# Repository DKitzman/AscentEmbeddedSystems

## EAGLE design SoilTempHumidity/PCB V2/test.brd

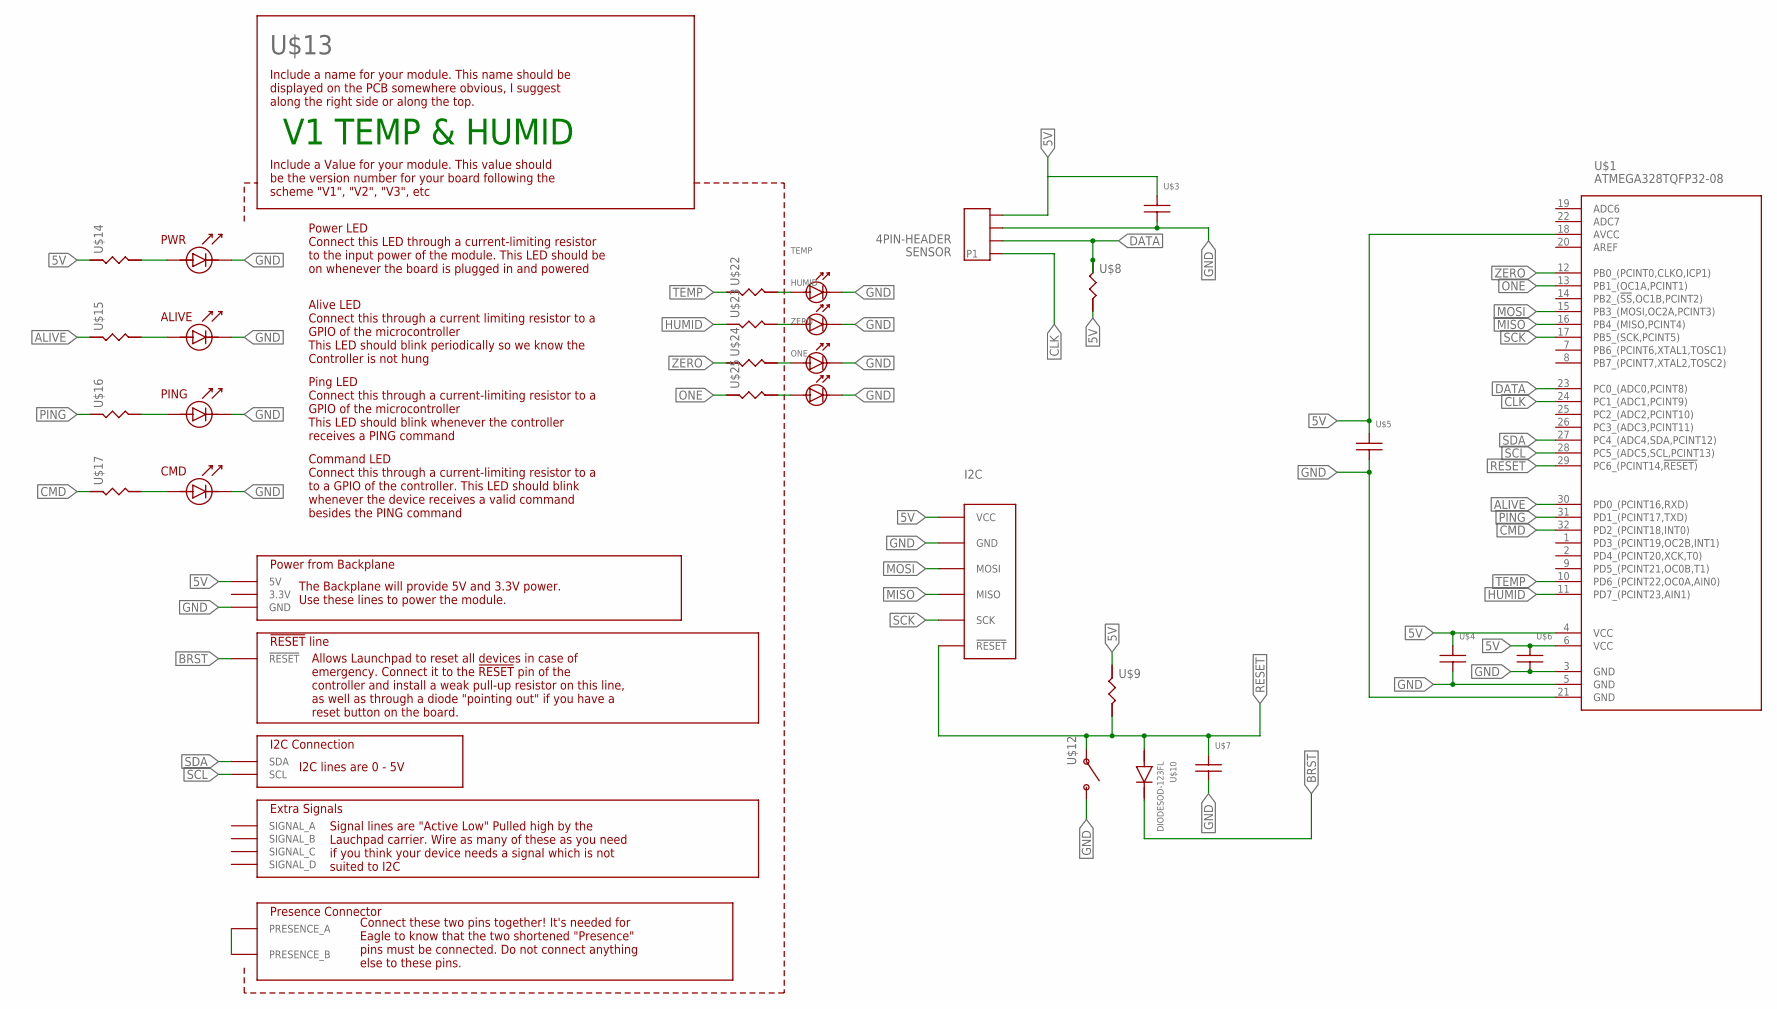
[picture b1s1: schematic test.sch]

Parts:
HUMID: LED; 0805_LED
I2C: ISP_PROGRAMMING_HEADER; 6PINHEADER_CORRECT
ONE: LED; 0805_LED
SENSOR: 4PIN-HEADER; 4HEADER_10MIL
TEMP: LED; 0805_LED
U$1: ATMEGA328TQFP32-08; TQFP32-08
U$3, U$4, U$5, U$6, U$7: CAPACITOR-UNPOLARIZED0805; 0805_STACKPOLERESISTOR
U$8, U$9, U$14, U$15, U$16, U$17, U$22, U$23, U$24, U$25: RESISTOR; 0805_STACKPOLERESISTOR
U$10: DIODESOD-123FL; SOD-123FL
U$12: PUSHBUTTONSMD; PUSHBUTTON_SMD
U$13: EMBEDDED_SUBSYSTEM_V2SMALL; SUBSYSTEM2016_V2-SMALL
ZERO: LED; 0805_LED

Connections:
5V: I2C.2 (VCC), SENSOR.P$4, U$1.4 (VCC), U$1.6 (VCC), U$1.18 (AVCC), U$3.P$1, U$4.P$1, U$5.P$1, U$6.P$1, U$8.P$2, U$9.P$1, U$13.B2 (5V), U$13.B3 (5V), U$14.P$1
ALIVE: U$1.30 (PD0_(PCINT16,RXD)), U$15.P$1
BRST: U$10.CATHODE, U$13.B5 (!RESET), U$13.B6 (!RESET)
CLK: SENSOR.P$1 (P1), U$1.24 (PC1_(ADC1,PCINT9))
CMD: U$1.32 (PD2_(PCINT18,INT0)), U$17.P$1
DATA: SENSOR.P$2, U$1.23 (PC0_(ADC0,PCINT8)), U$8.P$1
GND: HUMID.CATHODE, I2C.6 (GND), ONE.CATHODE, SENSOR.P$3, TEMP.CATHODE, U$1.3 (GND), U$1.5 (GND), U$1.21 (GND), U$3.P$2, U$4.P$2, U$5.P$2, U$6.P$2, U$7.P$2, U$12.3, U$13.A7 (GND), U$13.A8 (GND), U$13.A9 (GND), U$13.A10 (GND), U$13.ALIVELED_CATHODE, U$13.CMDLED_CATHODE, U$13.PINGLED_CATHODE, U$13.PWRLED_CATHODE, ZERO.CATHODE
HUMID: U$1.11 (PD7_(PCINT23,AIN1)), U$23.P$1
MISO: I2C.1 (MISO), U$1.16 (PB4_(MISO,PCINT4))
MOSI: I2C.4 (MOSI), U$1.15 (PB3_(MOSI,OC2A,PCINT3))
unnamed: U$13.A2 (PRESENCE_A), U$13.B17 (PRESENCE_B)
unnamed: U$13.PWRLED_ANODE, U$14.P$2
unnamed: U$13.ALIVELED_ANODE, U$15.P$2
unnamed: U$13.PINGLED_ANODE, U$16.P$2
unnamed: U$13.CMDLED_ANODE, U$17.P$2
unnamed: TEMP.ANODE, U$22.P$2
unnamed: HUMID.ANODE, U$23.P$2
unnamed: U$24.P$2, ZERO.ANODE
unnamed: ONE.ANODE, U$25.P$2
ONE: U$1.13 (PB1_(OC1A,PCINT1)), U$25.P$1
PING: U$1.31 (PD1_(PCINT17,TXD)), U$16.P$1
RESET: I2C.5 (!RESET), U$1.29 (PC6_(PCINT14,!RESET)), U$7.P$1, U$9.P$2, U$10.ANODE, U$12.1
SCK: I2C.3 (SCK), U$1.17 (PB5_(SCK,PCINT5))
SCL: U$1.28 (PC5_(ADC5,SCL,PCINT13)), U$13.B9 (SCL), U$13.B10 (SCL)
SDA: U$1.27 (PC4_(ADC4,SDA,PCINT12)), U$13.B7 (SDA), U$13.B8 (SDA)
TEMP: U$1.10 (PD6_(PCINT22,OC0A,AIN0)), U$22.P$1
ZERO: U$1.12 (PB0_(PCINT0,CLKO,ICP1)), U$24.P$1

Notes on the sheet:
V1 TEMP & HUMID

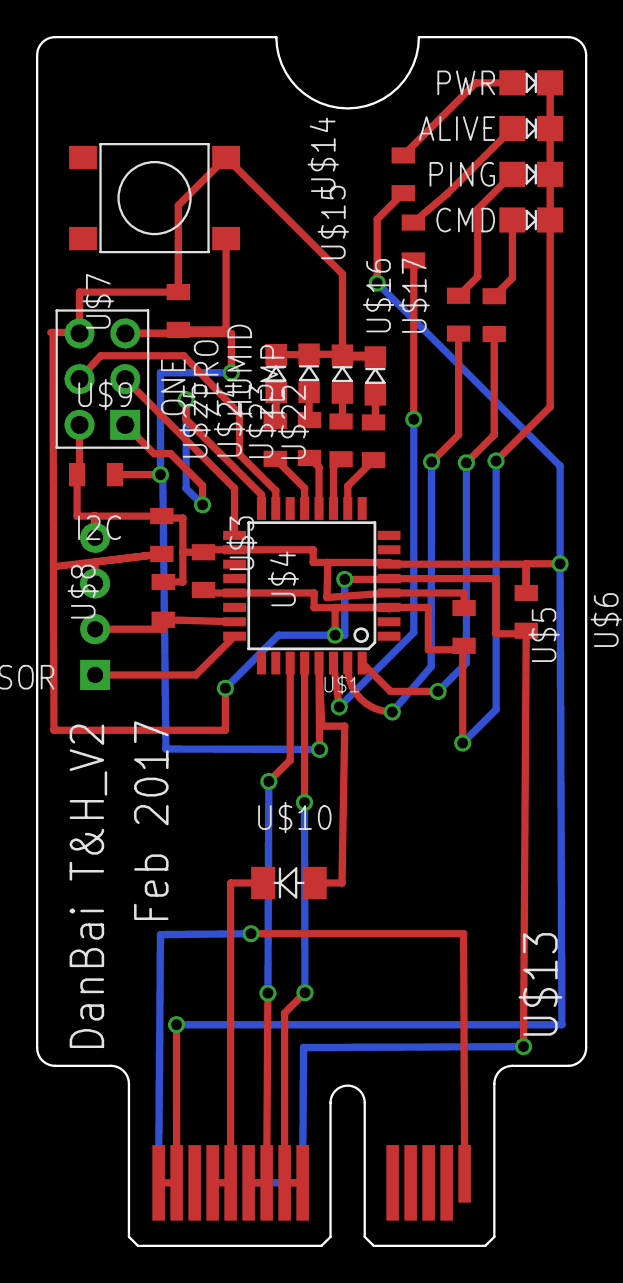
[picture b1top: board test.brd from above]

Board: 2 copper layers, 30.5 x 67.2 mm, 25 parts (0 on the bottom side), 27 nets.

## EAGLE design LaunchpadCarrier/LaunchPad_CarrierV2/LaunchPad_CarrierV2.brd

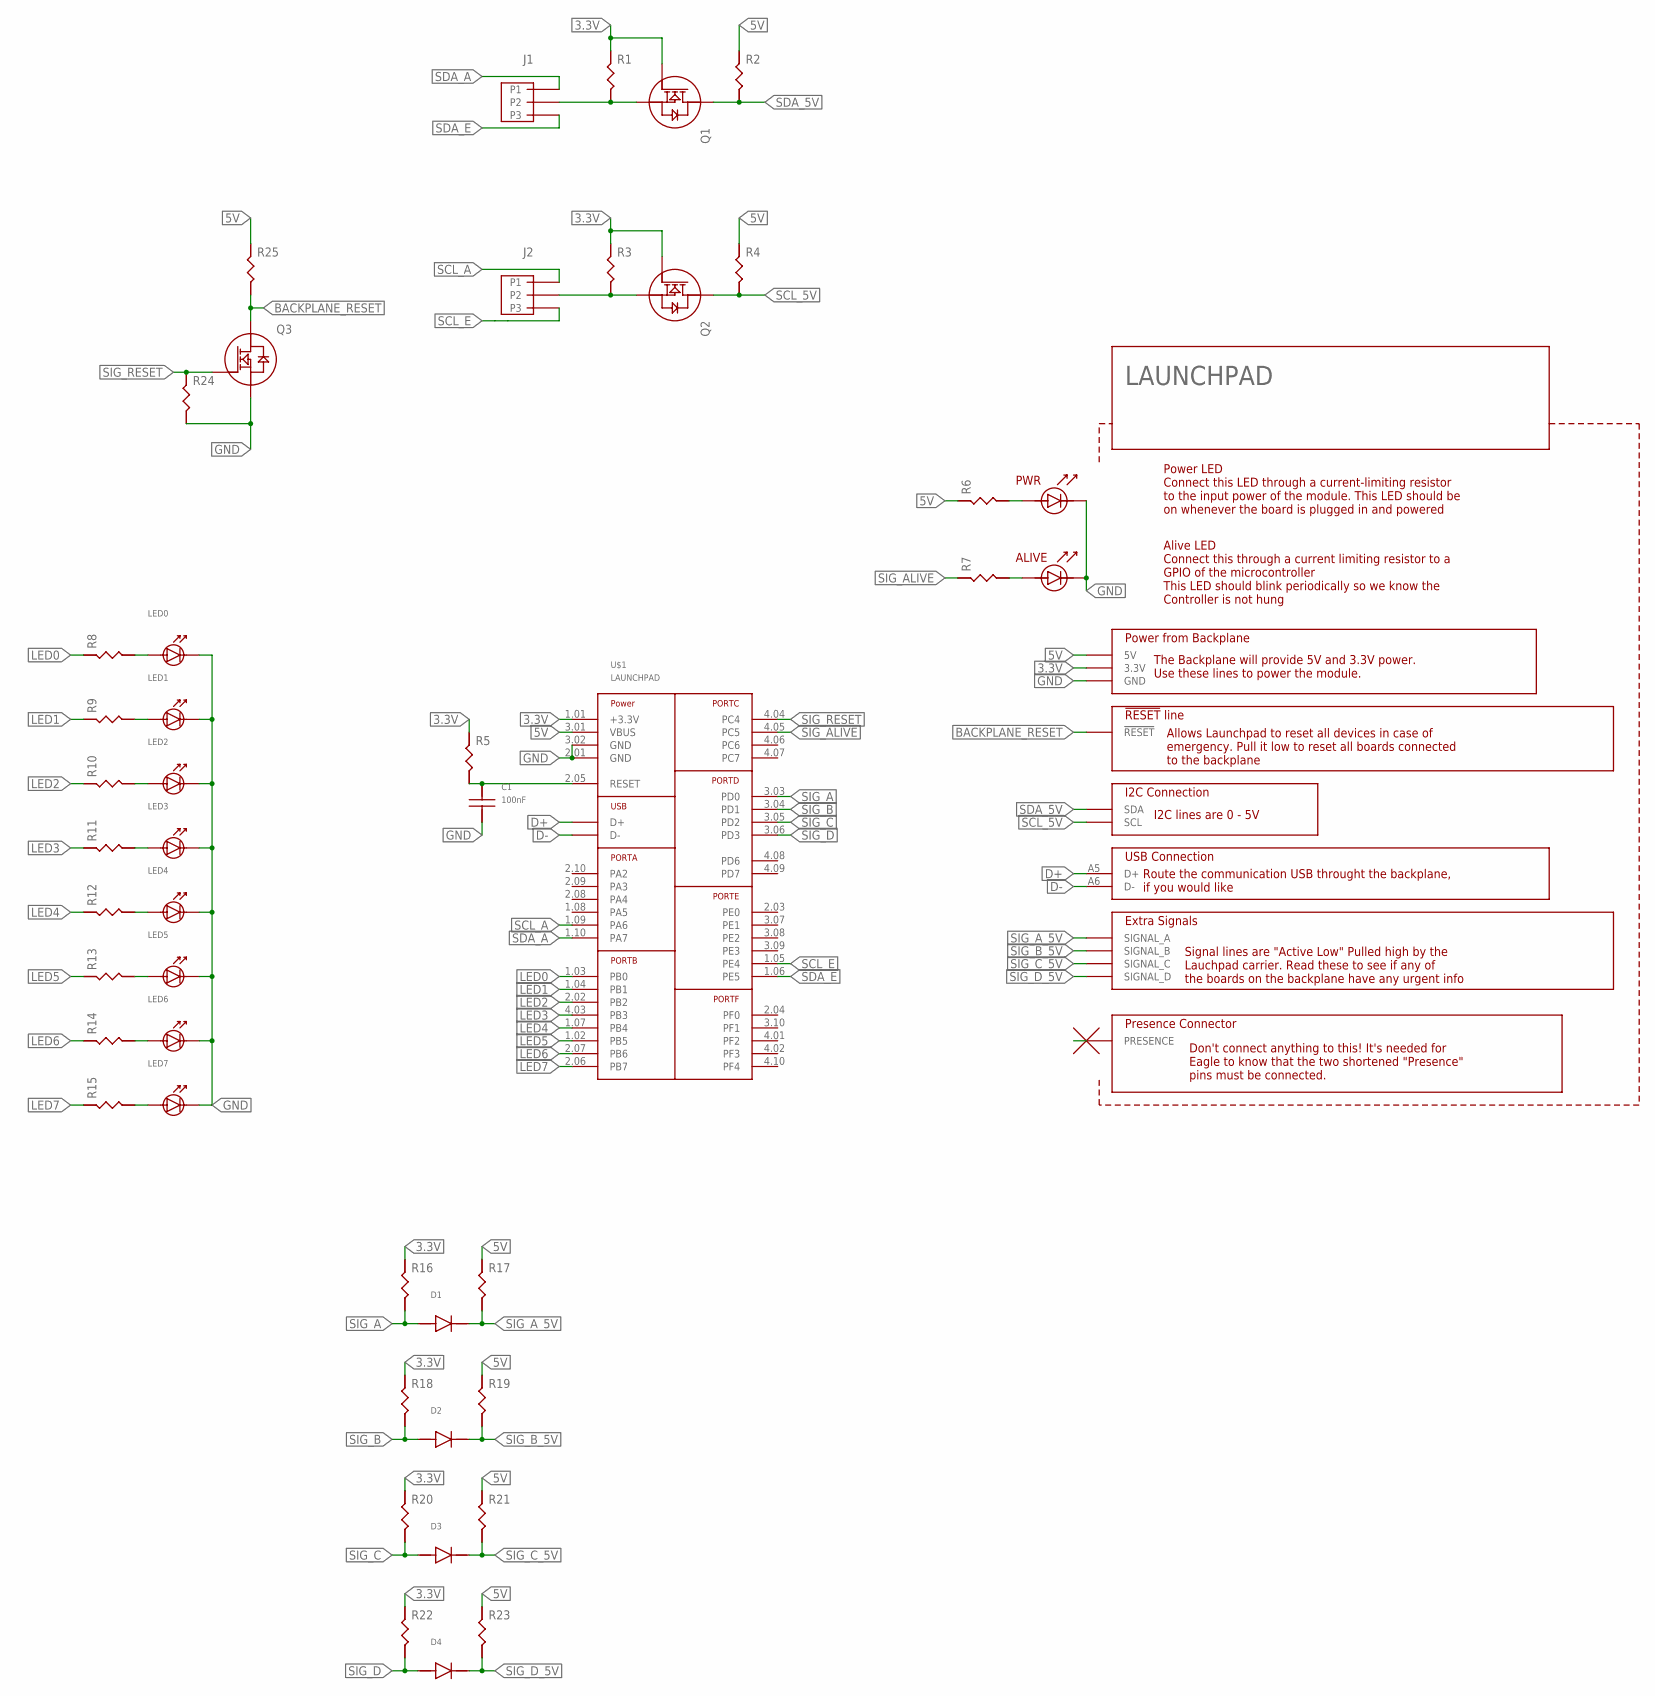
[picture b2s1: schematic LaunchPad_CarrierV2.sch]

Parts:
C1: 100nF; 0805_STACKPOLERESISTOR
D1, D2, D3, D4: DIODESOD-123FL; SOD-123FL
J1, J2: 3PIN_HEADER
LAUNCHPAD: LAUNCHPAD_CARRIERCARD; SUBSYSTEM2016_V2-LAUNCHPADCARRIER
LED0, LED1, LED2, LED3, LED4, LED5, LED6, LED7: LED; 0805_LED
Q1, Q2, Q3: NMOSSOT-23; SOT-23
R1, R2, R3, R4, R5, R6, R7, R8, R9, R10, R11, R12, R13, R14, R15, R16, R17, R18, R19, R20, R21, R22, R23, R24, R25: RESISTOR; 0805_STACKPOLERESISTOR
U$1: LAUNCHPAD

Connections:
3.3V: LAUNCHPAD.A3 (3.3V), LAUNCHPAD.A4 (3.3V), Q1.G (GATE), Q2.G (GATE), R1.P$1, R3.P$1, R5.P$1, R16.P$1, R18.P$1, R20.P$1, R22.P$1, U$1.1.01 (+3.3V)
5V: LAUNCHPAD.B2 (5V), LAUNCHPAD.B3 (5V), R2.P$1, R4.P$1, R6.P$1, R17.P$1, R19.P$1, R21.P$1, R23.P$1, R25.P$1, U$1.3.01 (VBUS)
BACKPLANE_RESET: LAUNCHPAD.B5 (!RESET), LAUNCHPAD.B6 (!RESET), Q3.D (DRAIN), R25.P$2
D+: LAUNCHPAD.A5 (D+), U$1.USB_D+ (D+)
D-: LAUNCHPAD.A6 (D-), U$1.USB_D- (D-)
GND: C1.P$2, LAUNCHPAD.A7 (GND), LAUNCHPAD.A8 (GND), LAUNCHPAD.A9 (GND), LAUNCHPAD.A10 (GND), LAUNCHPAD.ALIVELED_CATHODE, LAUNCHPAD.PWRLED_CATHODE, LED0.CATHODE, LED1.CATHODE, LED2.CATHODE, LED3.CATHODE, LED4.CATHODE, LED5.CATHODE, LED6.CATHODE, LED7.CATHODE, Q3.S (SOURCE), R24.P$2, U$1.2.01 (GND), U$1.3.02 (GND)
LED0: R8.P$1, U$1.1.03 (PB0)
LED1: R9.P$1, U$1.1.04 (PB1)
LED2: R10.P$1, U$1.2.02 (PB2)
LED3: R11.P$1, U$1.4.03 (PB3)
LED4: R12.P$1, U$1.1.07 (PB4)
LED5: R13.P$1, U$1.1.02 (PB5)
LED6: R14.P$1, U$1.2.07 (PB6)
LED7: R15.P$1, U$1.2.06 (PB7)
unnamed: LED0.ANODE, R8.P$2
unnamed: LAUNCHPAD.A2 (PRESENCE), LAUNCHPAD.B17 (PRESENCE)
unnamed: C1.P$1, R5.P$2, U$1.2.05 (RESET)
unnamed: LED1.ANODE, R9.P$2
unnamed: LED2.ANODE, R10.P$2
unnamed: LED3.ANODE, R11.P$2
unnamed: LED4.ANODE, R12.P$2
unnamed: LED5.ANODE, R13.P$2
unnamed: LED6.ANODE, R14.P$2
unnamed: LED7.ANODE, R15.P$2
unnamed: LAUNCHPAD.PWRLED_ANODE, R6.P$2
unnamed: LAUNCHPAD.ALIVELED_ANODE, R7.P$2
SCL_3.3V: J2.P2, Q2.S (SOURCE), R3.P$2
SCL_5V: LAUNCHPAD.B9 (SCL), LAUNCHPAD.B10 (SCL), Q2.D (DRAIN), R4.P$2
SCL_A: J2.P1, U$1.1.09 (PA6)
SCL_E: J2.P3, U$1.1.05 (PE4)
SDA_3.3V: J1.P2, Q1.S (SOURCE), R1.P$2
SDA_5V: LAUNCHPAD.B7 (SDA), LAUNCHPAD.B8 (SDA), Q1.D (DRAIN), R2.P$2
SDA_A: J1.P1, U$1.1.10 (PA7)
SDA_E: J1.P3, U$1.1.06 (PE5)
SIG_A: D1.ANODE, R16.P$2, U$1.3.03 (PD0)
SIG_ALIVE: R7.P$1, U$1.4.05 (PC5)
SIG_A_5V: D1.CATHODE, LAUNCHPAD.B13 (SIGNAL_A), LAUNCHPAD.B14 (SIGNAL_A), R17.P$2
SIG_B: D2.ANODE, R18.P$2, U$1.3.04 (PD1)
SIG_B_5V: D2.CATHODE, LAUNCHPAD.B15 (SIGNAL_B), LAUNCHPAD.B16 (SIGNAL_B), R19.P$2
SIG_C: D3.ANODE, R20.P$2, U$1.3.05 (PD2)
SIG_C_5V: D3.CATHODE, LAUNCHPAD.A13 (SIGNAL_C), LAUNCHPAD.A14 (SIGNAL_C), R21.P$2
SIG_D: D4.ANODE, R22.P$2, U$1.3.06 (PD3)
SIG_D_5V: D4.CATHODE, LAUNCHPAD.A15 (SIGNAL_D), LAUNCHPAD.A16 (SIGNAL_D), R23.P$2
SIG_RESET: Q3.G (GATE), R24.P$1, U$1.4.04 (PC4)

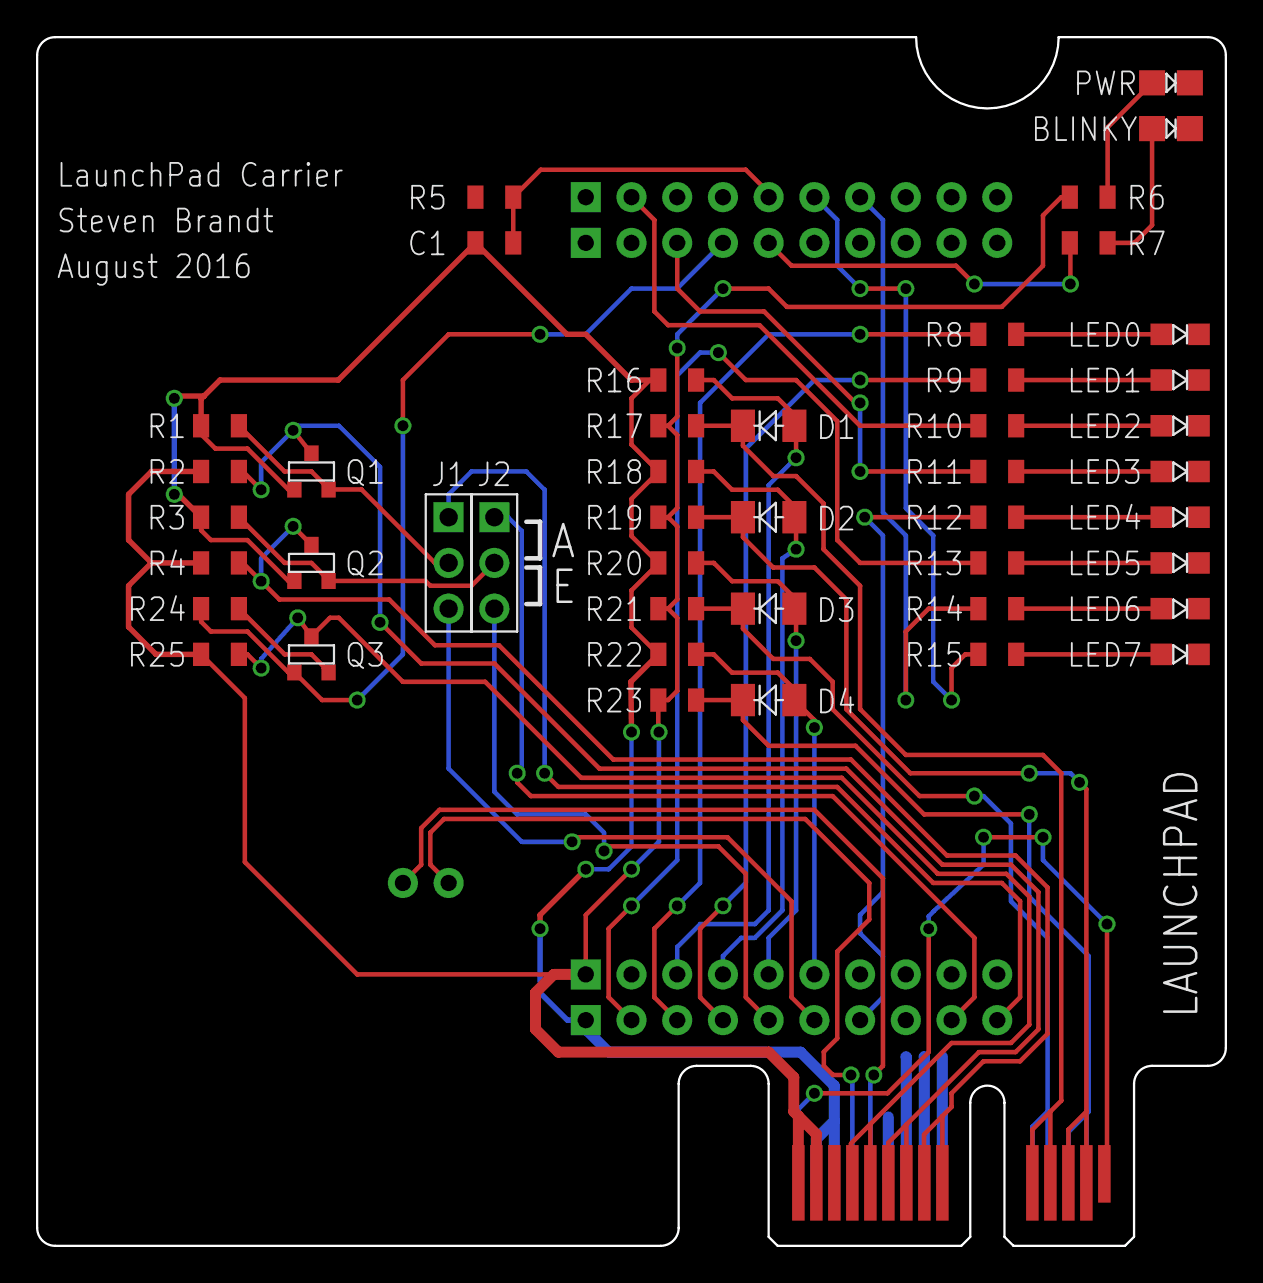
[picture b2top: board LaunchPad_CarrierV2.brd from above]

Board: 2 copper layers, 66.0 x 67.2 mm, 45 parts (0 on the bottom side), 44 nets.

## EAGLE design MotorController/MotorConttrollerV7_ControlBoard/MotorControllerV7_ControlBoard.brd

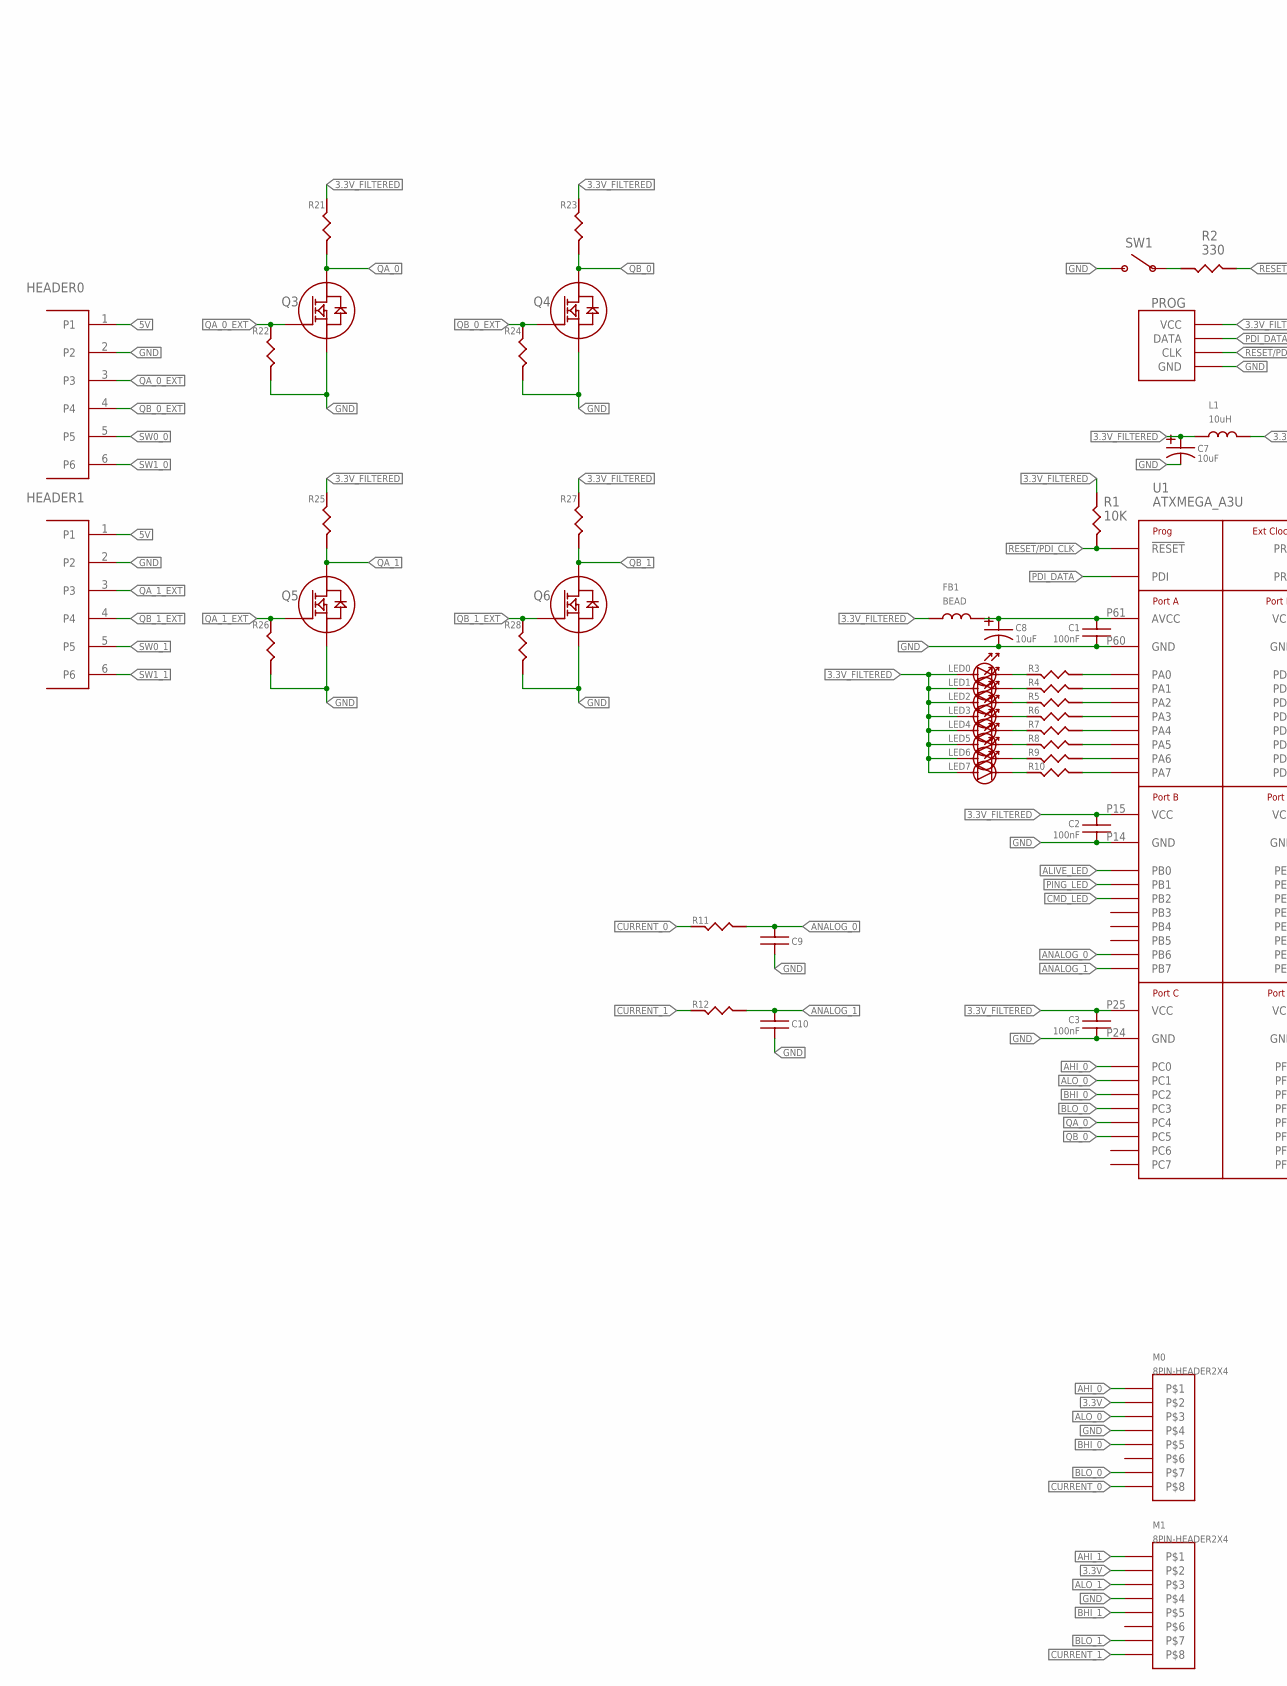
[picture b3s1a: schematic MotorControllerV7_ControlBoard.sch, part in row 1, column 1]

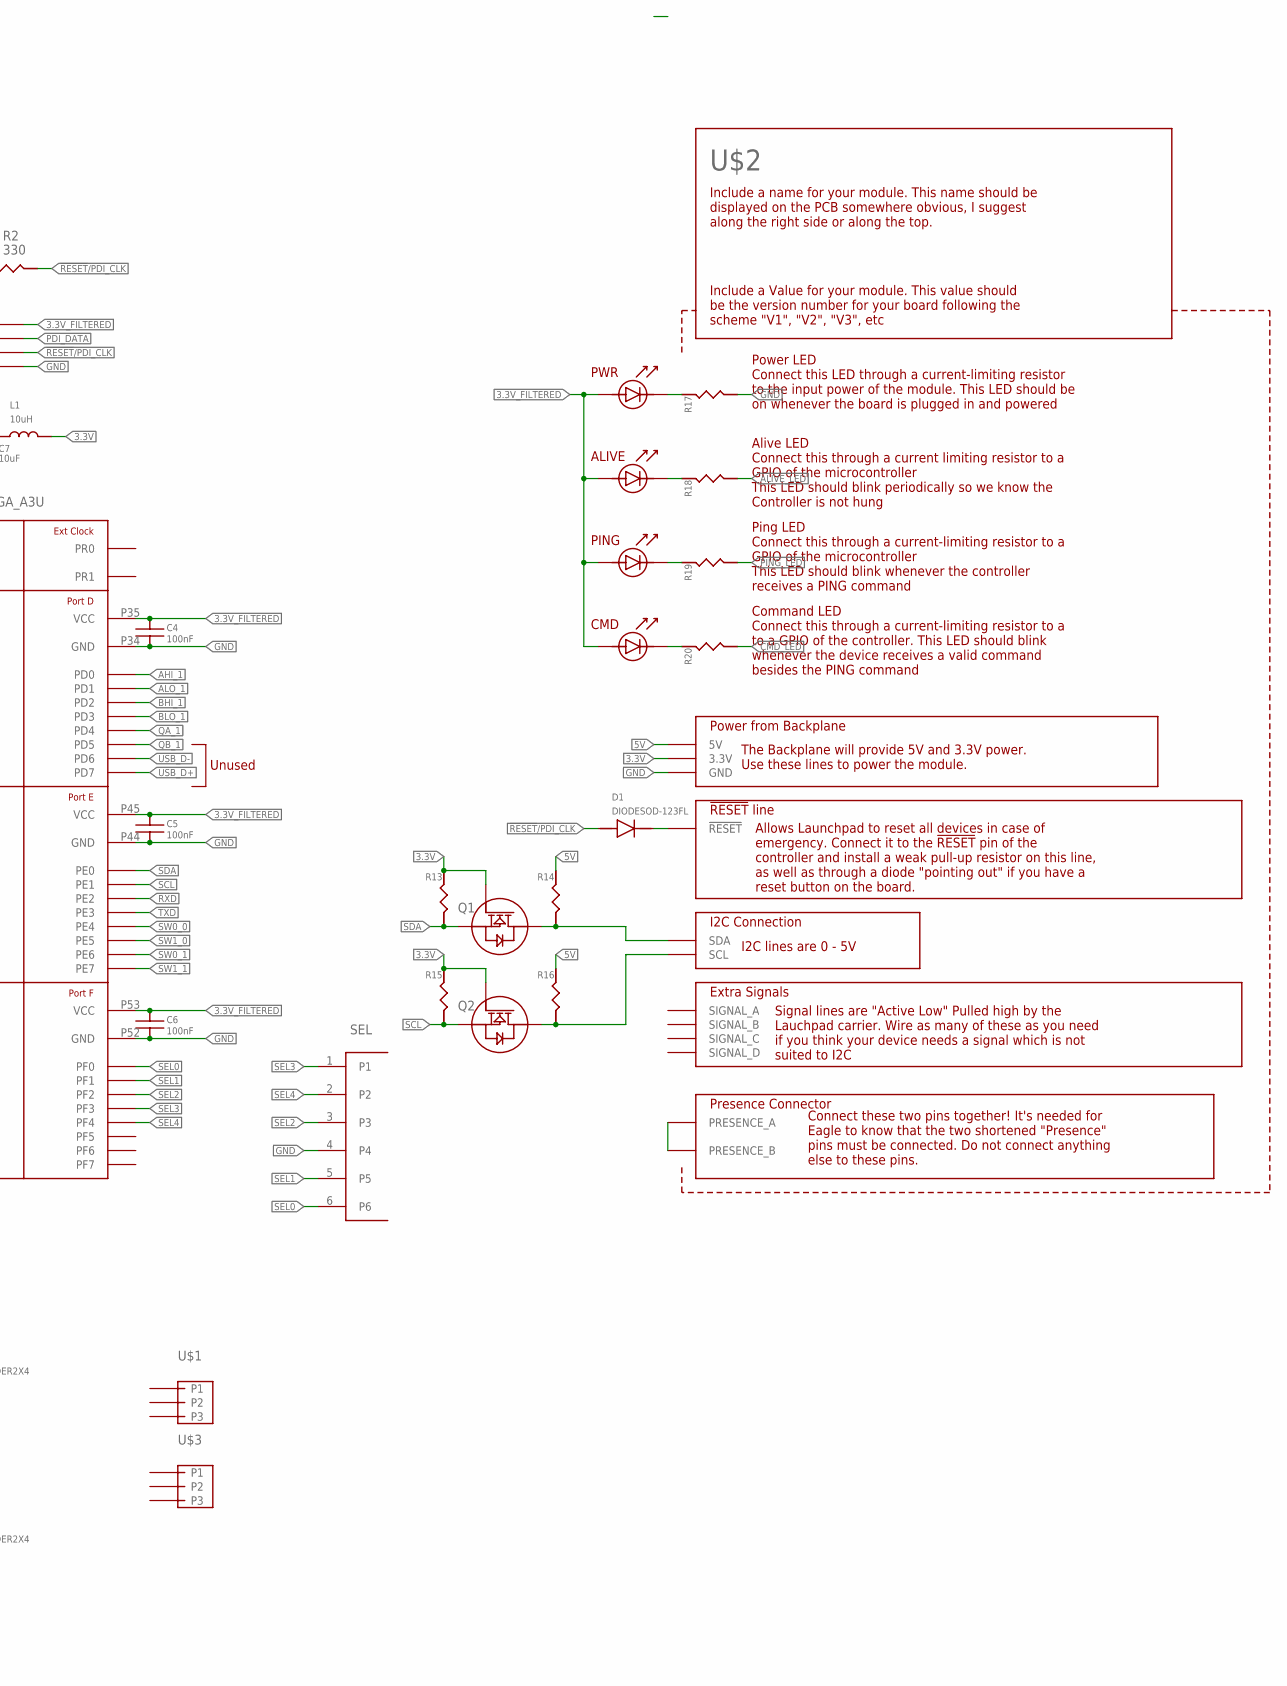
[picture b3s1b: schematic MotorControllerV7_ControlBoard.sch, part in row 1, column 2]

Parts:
C1, C2, C3, C4, C5, C6: 100nF; 0805_STACKPOLERESISTOR
C7, C8: 10uF; CAP_2MM
C9, C10: CAPACITOR-UNPOLARIZED0805; 0805_STACKPOLERESISTOR
D1: DIODESOD-123FL; SOD-123FL
FB1: BEAD; 0805_STACKPOLERESISTOR
HEADER0, HEADER1: 6PIN-HEADERMOLEX; 6PIN_MOLEX
L1: 10uH; 0805_STACKPOLERESISTOR
LED0, LED1, LED2, LED3, LED4, LED5, LED6, LED7: LED; 0805_LED
M0, M1: 8PIN-HEADER2X4; 8PIN_2X4
PROG: PDI_HEADER; 6PINHEADER_CORRECT
Q1, Q2, Q3, Q4, Q5, Q6: NMOSSOT-23; SOT-23
R1: 10K; 0805_STACKPOLERESISTOR
R2: 330; 0805_STACKPOLERESISTOR
R3, R4, R5, R6, R7, R8, R9, R10, R11, R12, R13, R14, R15, R16, R17, R18, R19, R20, R21, R22, R23, R24, R25, R26, R27, R28: RESISTOR; 0805_STACKPOLERESISTOR
SEL: 6PIN-HEADER2X3; 6PINHEADER_CORRECT
SW1: PUSHBUTTON; PUSHBUTTON(THROUGH-HOLE)
U1: ATXMEGA_A3U; 64-TQFP-0.8GRID
U$1, U$3: 3PIN_HEADER
U$2: EMBEDDED_SUBSYSTEM_V2MEDIUM; SUBSYSTEM2016_V2-MEDIUM

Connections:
3.3V: L1.P$2 (2), M0.2, M1.2, Q1.G (GATE), Q2.G (GATE), R13.P$2, R15.P$2, U$2.A3 (3.3V), U$2.A4 (3.3V)
3.3V_FILTERED: C2.P$1, C3.P$1, C4.P$1, C5.P$1, C6.P$1, C7.PLUS (POSITIVE_LEAD), FB1.P$1 (1), L1.P$1 (1), LED0.ANODE, LED1.ANODE, LED2.ANODE, LED3.ANODE, LED4.ANODE, LED5.ANODE, LED6.ANODE, LED7.ANODE, PROG.2 (VCC), R1.P$1, R21.P$2, R23.P$2, R25.P$2, R27.P$2, U1.P15 (VCC), U1.P25 (VCC), U1.P35 (VCC), U1.P45 (VCC), U1.P53 (VCC), U$2.ALIVELED_ANODE, U$2.CMDLED_ANODE, U$2.PINGLED_ANODE, U$2.PWRLED_ANODE
5V: HEADER0.1, HEADER1.1, R14.P$2, R16.P$2, U$2.B2 (5V), U$2.B3 (5V)
!RESET!/PDI_CLK: D1.ANODE, PROG.5 (CLK), R1.P$2, R2.P$2, U1.P57 (!RESET!)
AHI_0: M0.1, U1.P16 (PC0)
AHI_1: M1.1, U1.P26 (PD0)
ALIVE_LED: R18.P$1, U1.P6 (PB0)
ALO_0: M0.3, U1.P17 (PC1)
ALO_1: M1.3, U1.P27 (PD1)
ANALOG_0: C9.P$1, R11.P$2, U1.P12 (PB6)
ANALOG_1: C10.P$1, R12.P$2, U1.P13 (PB7)
BHI_0: M0.5, U1.P18 (PC2)
BHI_1: M1.5, U1.P28 (PD2)
BLO_0: M0.7, U1.P19 (PC3)
BLO_1: M1.7, U1.P29 (PD3)
CMD_LED: R20.P$1, U1.P8 (PB2)
CURRENT_0: M0.8, R11.P$1
CURRENT_1: M1.8, R12.P$1
GND: C1.P$2, C2.P$2, C3.P$2, C4.P$2, C5.P$2, C6.P$2, C7.MINUS (NEGATIVE_LEAD), C8.MINUS (NEGATIVE_LEAD), C9.P$2, C10.P$2, HEADER0.2, HEADER1.2, M0.4, M1.4, PROG.6 (GND), Q3.S (SOURCE), Q4.S (SOURCE), Q5.S (SOURCE), Q6.S (SOURCE), R17.P$1, R22.P$1, R24.P$1, R26.P$1, R28.P$1, SEL.4, SW1.3, U1.P14 (GND), U1.P24 (GND), U1.P34 (GND), U1.P44 (GND), U1.P52 (GND), U1.P60 (GND), U$2.A7 (GND), U$2.A8 (GND), U$2.A9 (GND), U$2.A10 (GND)
unnamed: R3.P$2, U1.P62 (PA0)
unnamed: C1.P$1, C8.PLUS (POSITIVE_LEAD), FB1.P$2 (2), U1.P61 (AVCC)
unnamed: R2.P$1, SW1.1
unnamed: R4.P$2, U1.P63 (PA1)
unnamed: R5.P$2, U1.P64 (PA2)
unnamed: R6.P$2, U1.P1 (PA3)
unnamed: R7.P$2, U1.P2 (PA4)
unnamed: R8.P$2, U1.P3 (PA5)
unnamed: R9.P$2, U1.P4 (PA6)
unnamed: R10.P$2, U1.P5 (PA7)
unnamed: LED0.CATHODE, R3.P$1
unnamed: LED1.CATHODE, R4.P$1
unnamed: LED2.CATHODE, R5.P$1
unnamed: LED3.CATHODE, R6.P$1
unnamed: LED4.CATHODE, R7.P$1
unnamed: LED5.CATHODE, R8.P$1
unnamed: LED6.CATHODE, R9.P$1
unnamed: LED7.CATHODE, R10.P$1
unnamed: R17.P$2, U$2.PWRLED_CATHODE
unnamed: U$2.A2 (PRESENCE_A), U$2.B17 (PRESENCE_B)
unnamed: D1.CATHODE, U$2.B5 (!RESET), U$2.B6 (!RESET)
unnamed: Q2.D (DRAIN), R16.P$1, U$2.B9 (SCL), U$2.B10 (SCL)
unnamed: Q1.D (DRAIN), R14.P$1, U$2.B7 (SDA), U$2.B8 (SDA)
unnamed: R20.P$2, U$2.CMDLED_CATHODE
unnamed: R19.P$2, U$2.PINGLED_CATHODE
unnamed: R18.P$2, U$2.ALIVELED_CATHODE
PDI_DATA: PROG.1 (DATA), U1.P56 (PDI)
PING_LED: R19.P$1, U1.P7 (PB1)
QA_0: Q3.D (DRAIN), R21.P$1, U1.P20 (PC4)
QA_0_EXT: HEADER0.3, Q3.G (GATE), R22.P$2
QA_1: Q5.D (DRAIN), R25.P$1, U1.P30 (PD4)
QA_1_EXT: HEADER1.3, Q5.G (GATE), R26.P$2
QB_0: Q4.D (DRAIN), R23.P$1, U1.P21 (PC5)
QB_0_EXT: HEADER0.4, Q4.G (GATE), R24.P$2
QB_1: Q6.D (DRAIN), R27.P$1, U1.P31 (PD5)
QB_1_EXT: HEADER1.4, Q6.G (GATE), R28.P$2
RXD: U1.P38 (PE2)
SCL: Q2.S (SOURCE), R15.P$1, U1.P37 (PE1)
SDA: Q1.S (SOURCE), R13.P$1, U1.P36 (PE0)
SEL0: SEL.6, U1.P46 (PF0)
SEL1: SEL.5, U1.P47 (PF1)
SEL2: SEL.3, U1.P48 (PF2)
SEL3: SEL.1, U1.P49 (PF3)
SEL4: SEL.2, U1.P50 (PF4)
SW0_0: HEADER0.5, U1.P40 (PE4)
SW0_1: HEADER1.5, U1.P42 (PE6)
SW1_0: HEADER0.6, U1.P41 (PE5)
SW1_1: HEADER1.6, U1.P43 (PE7)
TXD: U1.P39 (PE3)
USB_D+: U1.P33 (PD7)
USB_D-: U1.P32 (PD6)

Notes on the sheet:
Unused

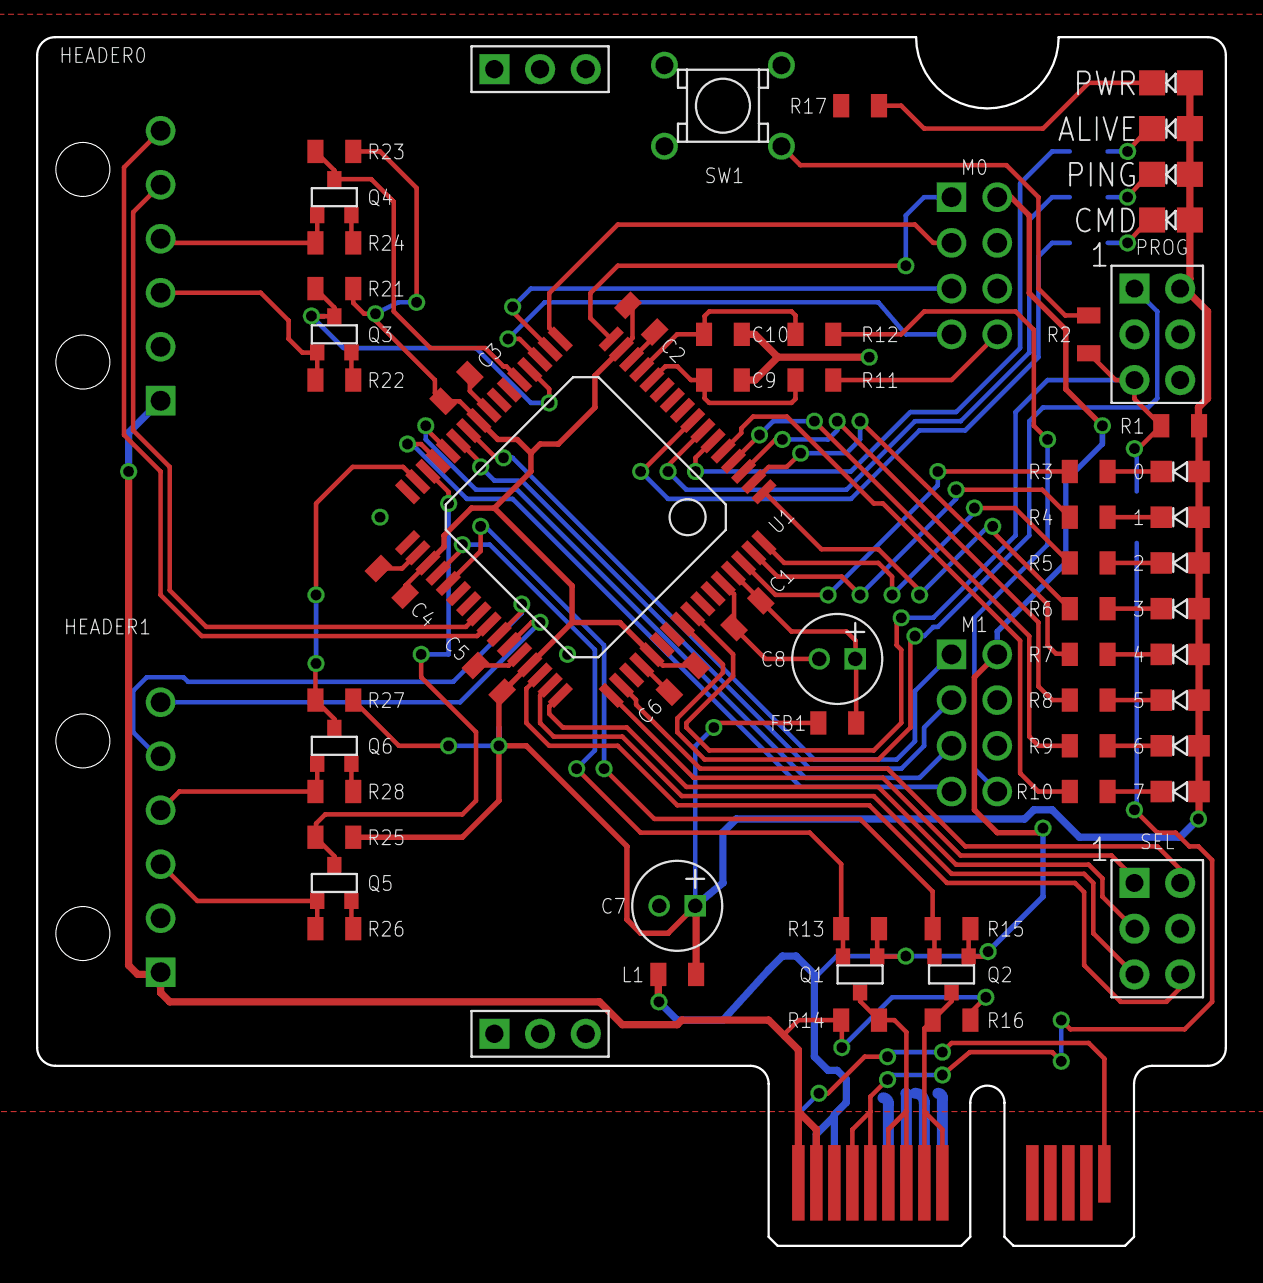
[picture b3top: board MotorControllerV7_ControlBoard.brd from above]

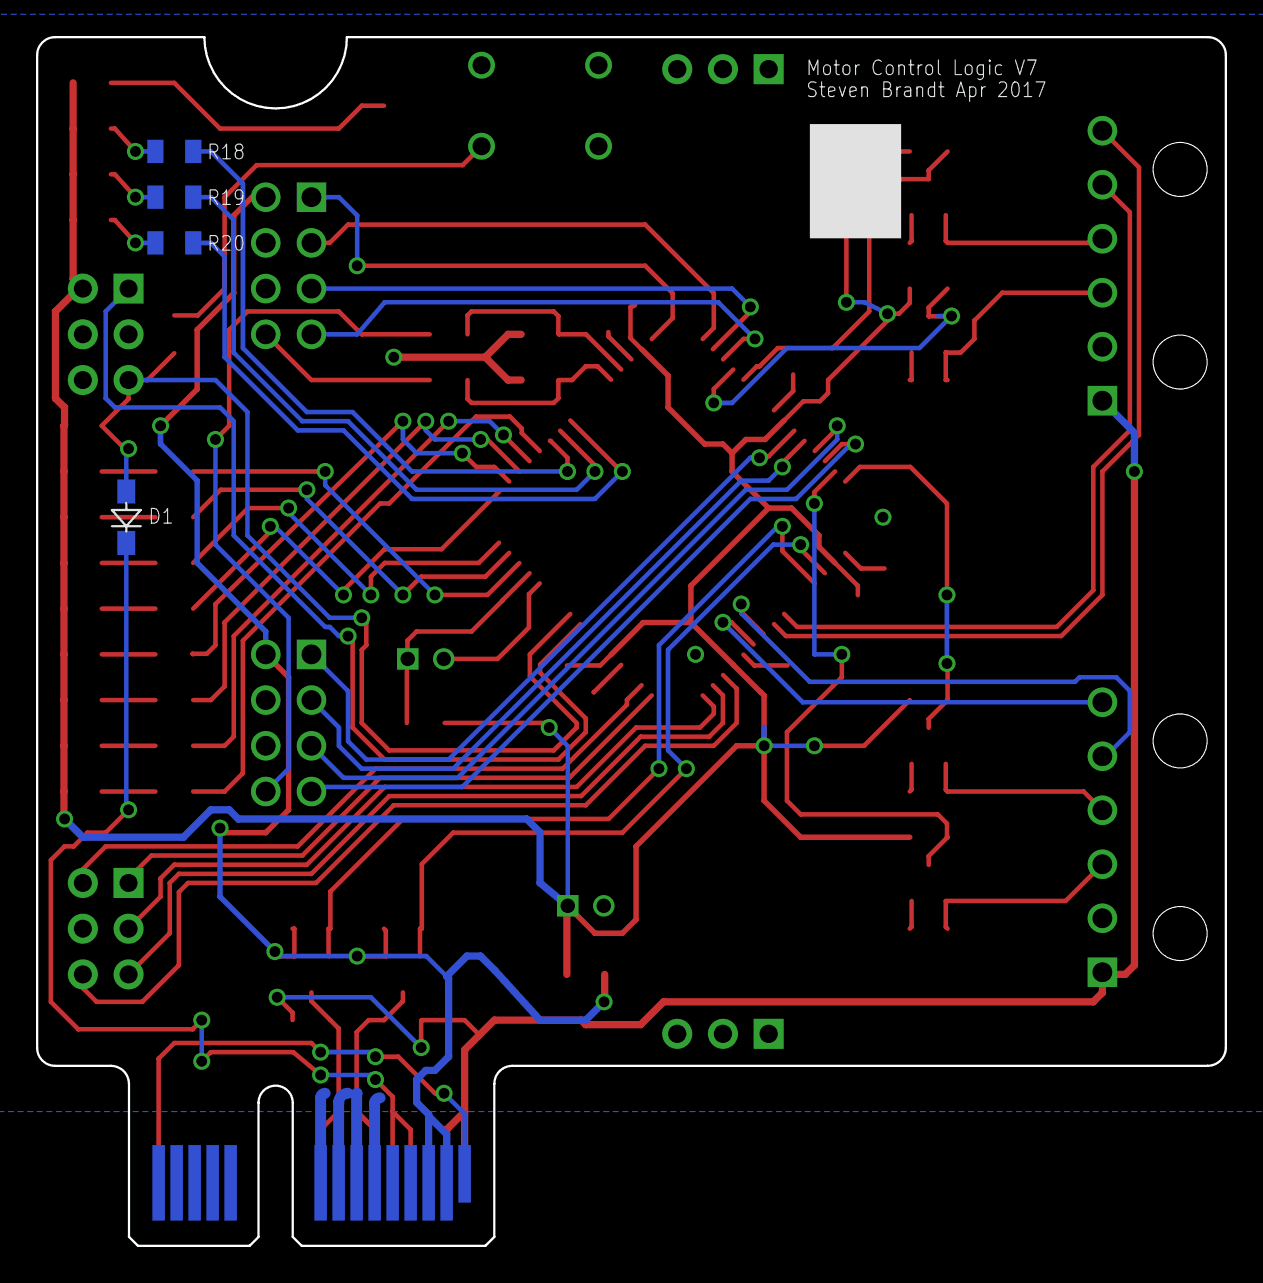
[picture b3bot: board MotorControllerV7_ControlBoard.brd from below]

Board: 2 copper layers, 66.0 x 67.2 mm, 66 parts (4 on the bottom side), 66 nets.
